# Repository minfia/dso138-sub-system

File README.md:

# DSO138 Sub System
DSO138の操作を少し楽にする"なにか"。

## 1. 環境
|  No.  |       名称       | バージョン |                             備考                              |
| :---: | ---------------- | ---------- | ------------------------------------------------------------- |
|   1   | Microchip Studio | 7.0.2594   |                                                               |
|   2   | ATmega_DFP       | 2.0.401    |                                                               |
|   3   | KiCad            | 7.0.6      | 回路図の一部は[自作](https://github.com/minfia/kicad-library) |

## 2. FUSEビット設定
| ビット名 |  値   |
| -------- | :---: |
| EXTENDED | 0xF9  |
| HIGH     | 0xDC  |
| LOW      | 0xE2  |

## 3. ビルド
1. `dso138_sub_system.atsln`をダブルクリック
1. `F7`を押下

## 4. ケースについて
一部目測による箇所があります。\
そのため基板と実際に出力されたケースの寸法が違う場合があります。

また、ケースの出力は遊舎工房様に[依頼](https://shop.yushakobo.jp/products/lasercut)したものになります。\
そのため、デザインファイル(`.svg`)は遊舎工房様向けとなっております。

## 5. ボタンの色詳解
|  No.  | 色  |       機能       |
| :---: | --- | ---------------- |
|   1   | 赤  | OK               |
|   2   | 黄  | 掃引時間         |
|   3   | 黄  | エッジ切り替え   |
|   4   | 黄  | トリガーレベル   |
|   5   | 黄  | 時間軸移動       |
|   6   | 黄  | 電圧移動         |
|   7   | 緑  | トリガー(auto)   |
|   8   | 緑  | トリガー(signal) |
|   9   | 青  | 波形保存         |
|  10   | 青  | 波形読み出し     |

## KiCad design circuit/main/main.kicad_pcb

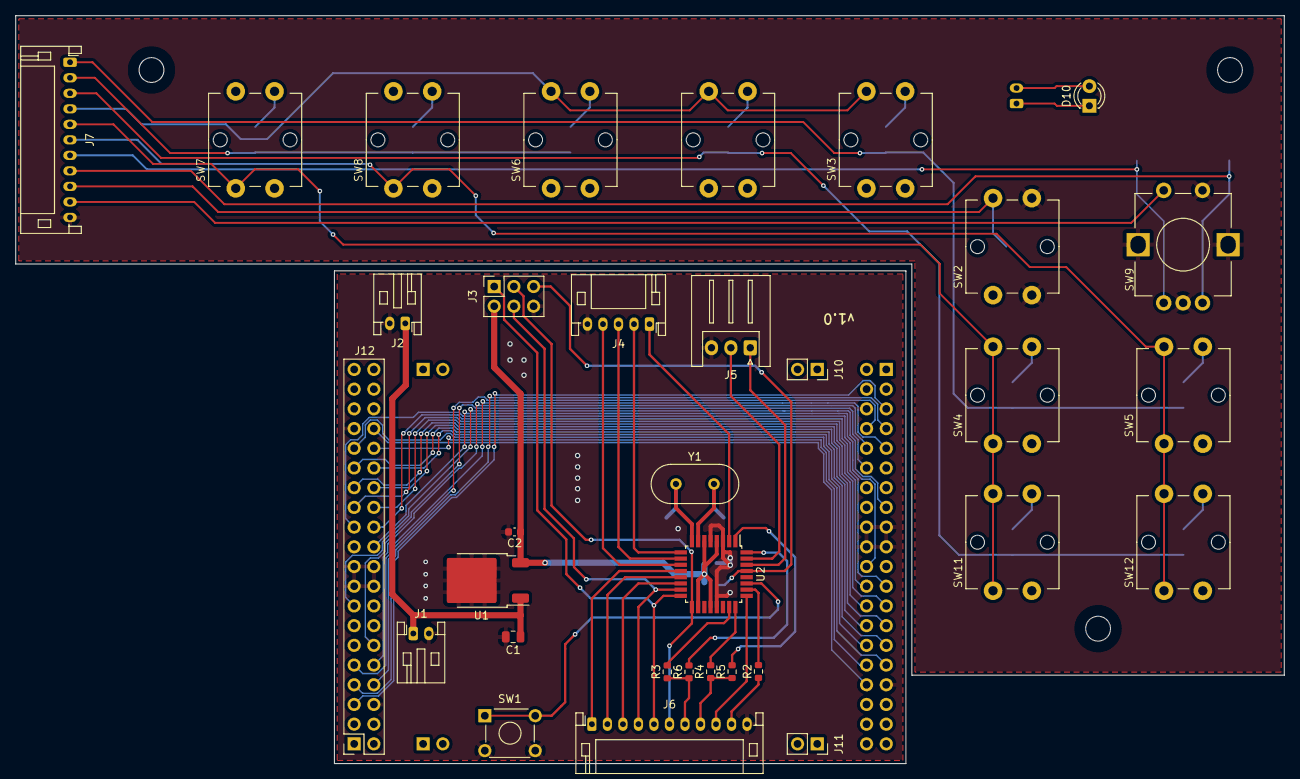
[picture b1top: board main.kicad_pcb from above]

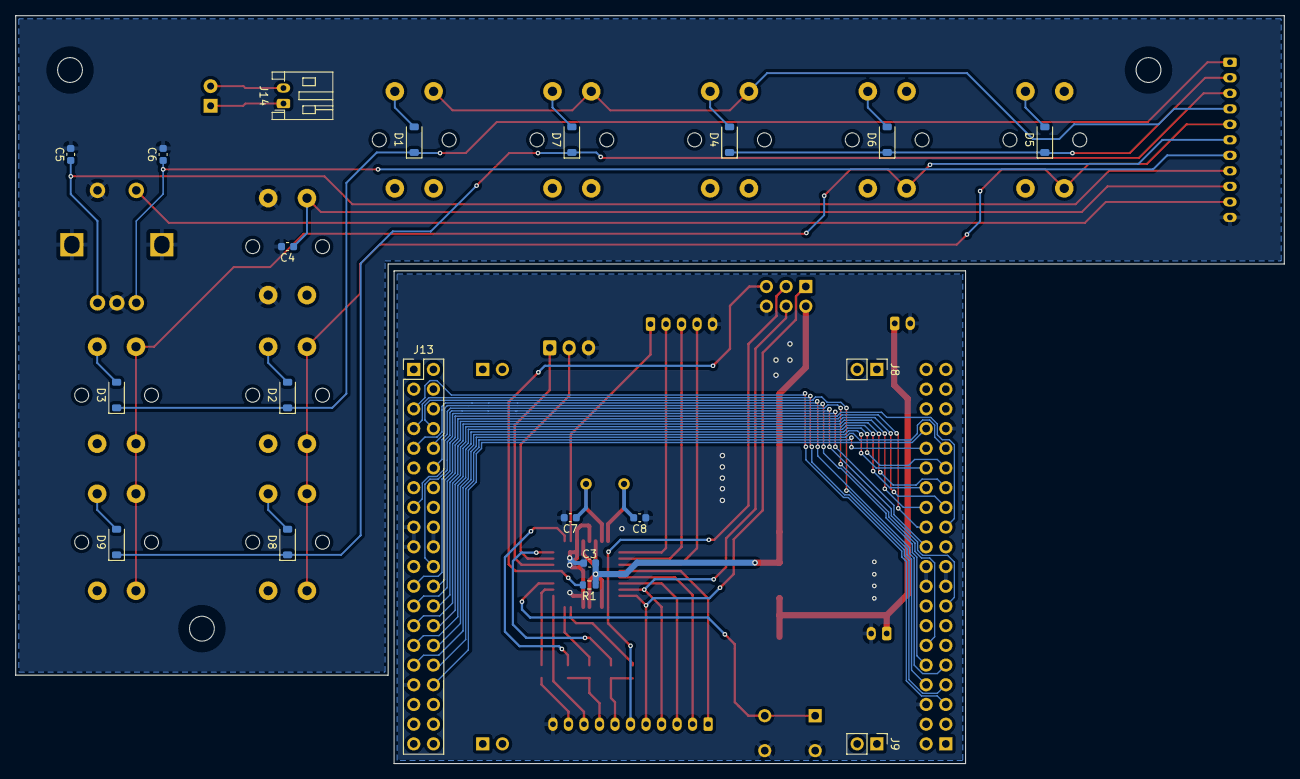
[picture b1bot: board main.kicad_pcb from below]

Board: 2 copper layers, 163.5 x 96.4 mm, 53 parts (20 on the bottom side), 69 nets.

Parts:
C1: 0.33uF; C_0805_2012Metric
C2: 2.2uF; C_0603_1608Metric
C3, C4, C5, C6: 0.1uF; C_0603_1608Metric
C7, C8: 22pF; C_0603_1608Metric
D1, D2, D3, D4, D5, D6, D7, D8, D9: 1N4148; D_SOD-123
D10: LED; LED_D3.0mm
J1, J2, J14: Conn_01x02; JST_PH_S2B-PH-K_1x02_P2.00mm_Horizontal
J3: AVR-ISP-6; PinSocket_2x03_P2.54mm_Vertical
J4: PH-1x5pin_Horizontal; JST_PH_S5B-PH-K_1x05_P2.00mm_Horizontal
J5: XH-1x3pin_Horizontal; JST_XH_S3B-XH-A_1x03_P2.50mm_Horizontal
J6, J7: PH-1x11pin_Horizontal; JST_PH_S11B-PH-K_1x11_P2.00mm_Horizontal
J8, J9: Conn_01x02; PinHeader_1x02_P2.54mm_Vertical
J10, J11: Conn_01x02; PinSocket_1x02_P2.54mm_Vertical
J12: Conn_02x20_Odd_Even; PinSocket_2x20_P2.54mm_Vertical
J13: Conn_02x20_Odd_Even; PinHeader_2x20_P2.54mm_Vertical
R1: 10k; R_0603_1608Metric
R2: 100; R_0603_1608Metric
R3, R4, R5, R6: 0; R_0603_1608Metric
SW1: SW_MEC_5E; SW_TH_Tactile_Omron_B3F-10xx
SW2: KC-901TC-R
SW3, SW6, SW7, SW8, SW10: KC-901TC-Y
SW4, SW5: KC-901TC-G
SW9: EC12PLxVF; EC12-020
SW11, SW12: KC-901TC-BU
U1: NJM2845DL1-05; TO-252-2
U2: ATmega328P-A; TQFP-32_7x7mm_P0.8mm
Y1: 16MHz; Crystal_HC18-U_Vertical

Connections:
+5V: C2.1, C3.1, J3.2 (VCC), R1.1, U1.3 (VOUT), U2.4 (VCC), U2.6 (VCC), U2.18 (AVCC), U2.20 (AREF)
+9V: C1.1, J1.1, J2.1, U1.1 (VIN)
GND: C1.2, C2.2, C3.2, C7.2, C8.2, J1.2, J2.2, J3.6 (GND), J4.5, J5.3, J6.11, J12.6, J12.17, J12.18, J12.19, J12.20, J12.33, J13.6, J13.17, J13.18, J13.19, J13.20, J13.33, SW1.2, U1.2 (GND), U2.3 (GND), U2.5 (GND), U2.21 (GND)
GND1: C4.2, C5.2, C6.2, J7.11, SW2.3 (K), SW2.4 (A), SW9.-, SW9.C, SW9.GND
unnamed: D1.2 (A), SW3.4 (A)
unnamed: D1.1 (K), D2.1 (K), D3.1 (K), J7.1
unnamed: D2.2 (A), SW4.4 (A)
unnamed: D3.2 (A), SW5.4 (A)
unnamed: D4.2 (A), SW6.4 (A)
unnamed: D4.1 (K), D5.1 (K), D6.1 (K), J7.2
unnamed: D5.2 (A), SW7.4 (A)
unnamed: D6.2 (A), SW8.4 (A)
unnamed: D7.2 (A), SW10.4 (A)
unnamed: D7.1 (K), D8.1 (K), D9.1 (K), J7.3
unnamed: D8.2 (A), SW11.4 (A)
unnamed: D9.2 (A), SW12.4 (A)
unnamed: D10.2 (A), J14.2
unnamed: D10.1 (K), J14.1
unnamed: J3.1 (MISO), J6.5, U2.16 (PB4)
unnamed: J3.4 (MOSI), J6.4, U2.15 (PB3)
unnamed: J3.3 (SCK), J6.6, U2.17 (PB5)
unnamed: J3.5 (~RST), R1.2, U2.29 (~RESET/PC6)
unnamed: J4.1, U2.2 (PD4)
unnamed: J4.2, U2.9 (PD5)
unnamed: J4.3, U2.10 (PD6)
unnamed: J4.4, U2.11 (PD7)
unnamed: J5.1, U2.30 (PD0)
unnamed: J5.2, U2.31 (PD1)
unnamed: J6.1, U2.12 (PB0)
unnamed: J6.2, U2.13 (PB1)
unnamed: J6.3, U2.14 (PB2)
unnamed: J6.7, R3.1, R6.1
unnamed: J6.8, R4.1, R5.1
unnamed: J6.9, U2.25 (PC2)
unnamed: J6.10, R2.1
unnamed: J7.4, SW3.2, SW6.2, SW10.2
unnamed: J7.5, SW4.1, SW4.2, SW7.1, SW11.1, SW11.2
unnamed: J7.6, SW5.1, SW5.2, SW8.1, SW12.1, SW12.2
unnamed: C6.1, J7.7, SW9.A
unnamed: C5.1, J7.8, SW9.B
unnamed: C4.1, J7.9, SW2.2
unnamed: J7.10, SW9.+
unnamed: J12.5, J13.5
unnamed: J12.7, J13.7
unnamed: J12.8, J13.8
unnamed: J12.9, J13.9
unnamed: J12.10, J13.10
unnamed: J12.12, J13.12
unnamed: J12.15, J13.15
unnamed: J12.22, J13.22
unnamed: J12.23, J13.23
unnamed: J12.24, J13.24
unnamed: J12.25, J13.25
unnamed: J12.26, J13.26
unnamed: J12.27, J13.27
unnamed: J12.28, J13.28
unnamed: J12.29, J13.29
unnamed: J12.30, J13.30
unnamed: J12.31, J13.31
unnamed: J12.32, J13.32
unnamed: J12.34, J13.34
unnamed: R3.2, U2.23 (PC0)
unnamed: R4.2, U2.24 (PC1)
unnamed: R2.2, U2.26 (PC3)
unnamed: SW1.1, U2.27 (PC4)
unnamed: R6.2, U2.32 (PD2)
unnamed: R5.2, U2.1 (PD3)
unnamed: C7.1, U2.7 (XTAL1/PB6), Y1.2
unnamed: C8.1, U2.8 (XTAL2/PB7), Y1.1

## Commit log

2023-02-12 add: DSO138を制御できる機能を一通り追加
2023-05-07 Change: マイコンのシリーズをATmega128からATmega328Pに変更
2024-03-21 fix: 回路に合わせて入出力を修正
2024-03-21 add: 回路のプロジェクトを追加
2024-03-21 add: ケースのデザインデータを追加
2024-03-21 add: ライセンスファイルを追加
2024-03-21 docs: 情報追記
2024-03-21 upgrade: v0.0.1 -> v1.0.0
2025-03-14 docs: README.md
